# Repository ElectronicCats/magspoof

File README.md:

# MagSpoof By Electronic Cats
  
<a href="https://github.com/ElectronicCats/magspoof/wiki">

<p align=center>

</p>

<p align=center>
Also available at distributors:
</p>
<p align=center>

</p>

# What is MagSpoof?

**MagSpoof by Electronic Cats** is a device that can spoof/emulate any magnetic stripe or credit card. It can work "wirelessly", even on **standard magstripe/credit card readers**, by generating a strong electromagnetic field that emulates a traditional magnetic stripe card.

* Allows you to store all of your credit cards and magstripes in one device
* Works on traditional magstripe readers **wirelessly** (no NFC/RFID required)
* Can **disable** Chip-and-PIN (code not included)
* Correctly **predicts** Amex credit card numbers + expirations from previous card number (code not included)
* Supports all three magnetic stripe tracks, and even supports Track 1+2 simultaneously
* Easy to build using Arduino or other common parts

MagSpoof can be used as a traditional credit card and simply store all of your credit cards (and with modification, can technically disable chip requirements) in various impressive and exciting form factors, or can be used for security research in any area that would traditionally require a magstripe, such as readers for credit cards, drivers licenses, hotel room keys, automated parking lot tickets, etc.

**Note**: The Chip-and-PIN and Amex information is **not** implemented and using MagSpoof requires you to have/own the magstripes that you wish to emulate. Simply having a credit card number and expiration is not enough to perform transactions. MagSpoof **does** allow you to perform research in other areas of magstripes, microcontrollers, and electromagnetism, as well as learn about and create your own devices similar to other existing, commercial technologies such as <a href="http://www.samsung.com/us/support/answer/ANS00043865/997410383/">Samsung MST</a> and <a href="https://onlycoin.com/">Coin</a>.</p>

### ⚠️ Disclaimer ⚠️
MagSpoof is a wireless penetration testing tool intended solely for use in authorized security audits, where such usage is permitted by applicable laws and regulations. Before utilizing this tool, it is crucial to ensure compliance with all relevant legal requirements and obtain appropriate permissions from the relevant authorities.

It is essential to notice that the board does not provide any means or authorization to utilize credit cards or engage in any financial transactions that are not legally authorized. Electronic Cats holds no responsibility for any unauthorized use of the tool or any resulting damages.

-----

# Based in work of Samy Kamkar

**Point of Contact:** [@SamyKamkar](https://twitter.com/samykamkar)

You can see more of my projects at <http://samy.pl> or contact me at <code@samy.pl>.

------

## How to contribute 
 Contributions are welcome! 

Please read the document  [**Contribution Manual**](https://github.com/ElectronicCats/electroniccats-cla/blob/main/electroniccats-contribution-manual.md)  which will show you how to contribute your changes to the project.

✨ Thanks to all our [contributors](https://github.com/ElectronicCats/magspoof/graphs/contributors)! ✨

See  [**_Electronic Cats CLA_**](https://github.com/ElectronicCats/electroniccats-cla/blob/main/electroniccats-cla.md) for more information.

See the [**community code of conduct**](https://github.com/ElectronicCats/electroniccats-cla/blob/main/electroniccats-community-code-of-conduct.md)   for a vision of the community we want to build and what we expect from it.

### Maintainer

Electronic Cats invests time and resources in providing this open-source design design, please support Electronic Cats and open-source hardware by purchasing products from Electronic Cats!

# License

Electronic Cats invests time and resources in providing this open-source design. Please support Electronic Cats and open-source hardware by purchasing products from Electronic Cats!

Designed by Electronic Cats.

Firmware released under an GNU AGPL v3.0 license. See the LICENSE file for more information.

Hardware released under an CERN Open Hardware Licence v1.2. See the LICENSE_HARDWARE file for more information.

Electronic Cats is a registered trademark, please do not use if you sell these PCBs.

30 Octuber 2019

------

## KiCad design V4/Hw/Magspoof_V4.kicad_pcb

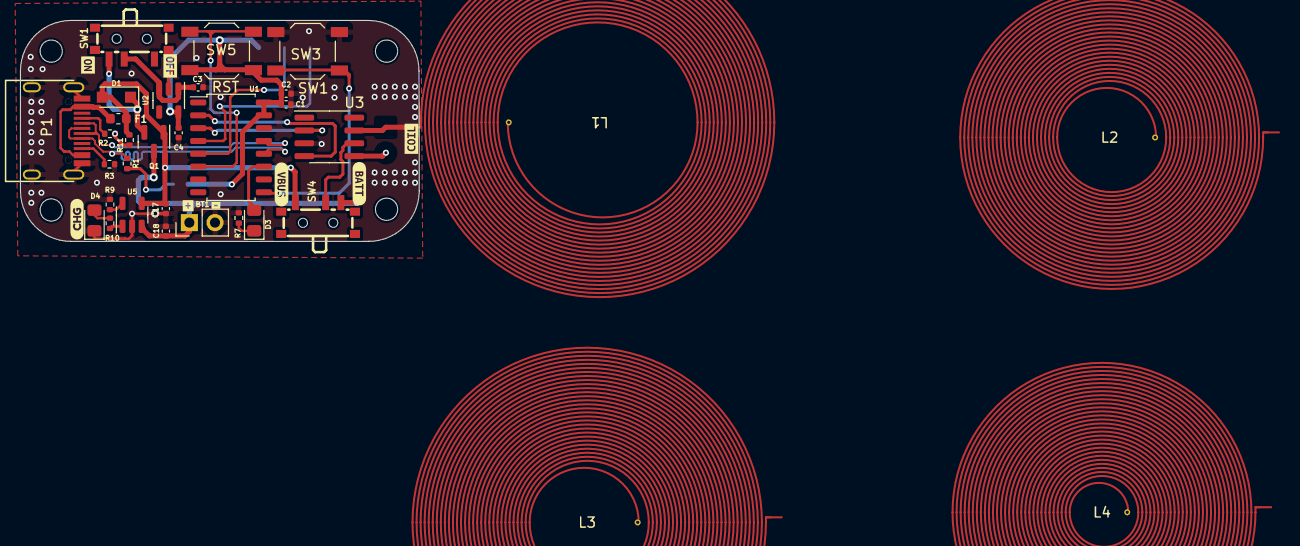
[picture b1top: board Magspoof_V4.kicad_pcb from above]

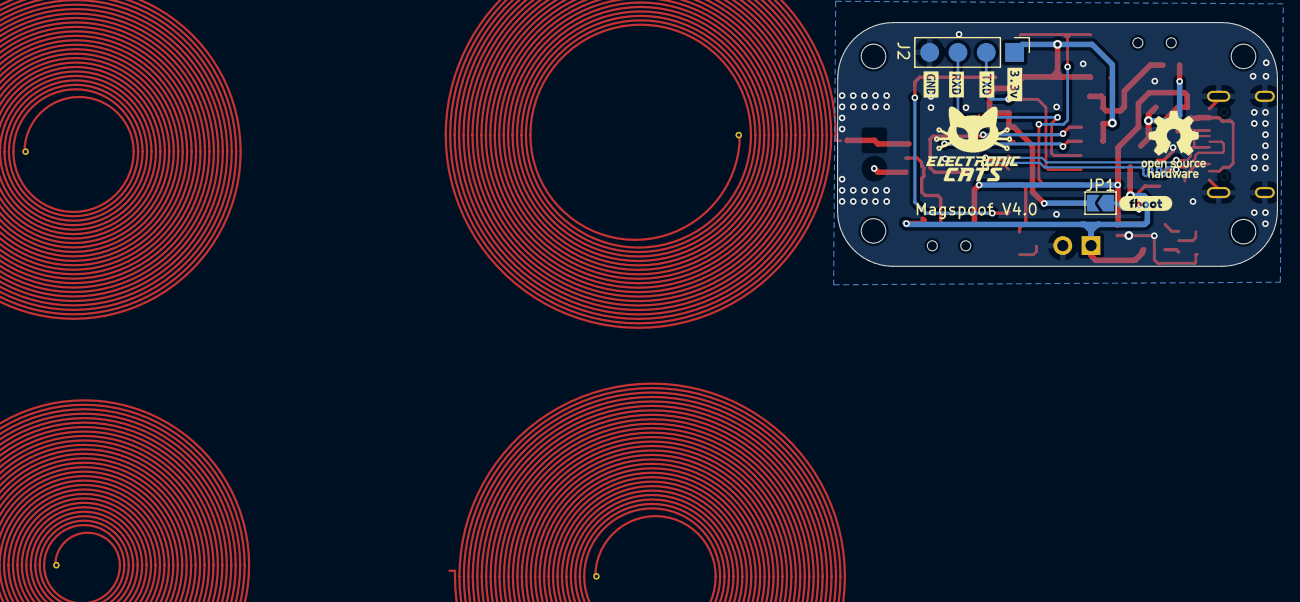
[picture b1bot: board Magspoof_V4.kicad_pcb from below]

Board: 2 copper layers, 39.5 x 21.9 mm, 51 parts (7 on the bottom side), 25 nets.

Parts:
BT1: Battery_Cell; PinHeader_1x02_P2.54mm_Vertical
C1, C2: 0.1uF; C_0402_1005Metric
C3, C4, C17, C18: 10uF; C_0402_1005Metric
D1: MBR120; D_SOD-123F
D3: Status; LED_0805_2012Metric_Pad1.15x1.40mm_HandSolder
D4: CHG; LED_0805_2012Metric_Pad1.15x1.40mm_HandSolder
F1: 0.5A; Fuse_0603_1608Metric
H1, H2, H3, H4: MountingHole; MountingHole_2.2mm_M2
J2: SWD; PinHeader_1x04_P2.54mm_Vertical
JP1: boot; SolderJumper-2_P1.3mm_Open_TrianglePad1.0x1.5mm
L1: 20t_35mm; Coil_20t_35mm_0.2_0.2_0.6_0.3
L2: 25t_30mm; Coil_25t_30mm_0.2_0.2_0.6_0.3
L3: 30t_35mm; Coil_30t_35mm_0.2_0.2_0.6_0.3
L4: 30t_30mm; Coil_30t_30mm_0.2_0.2_0.6_0.3
P1: USB_C_Plug_USB2.0; C393939
Q1: DMG3415U-7; SOT-23
R1: 20K; R_0402_1005Metric
R2, R3, R9: 5.1k; R_0402_1005Metric
R7: 180R; R_0402_1005Metric
R10: 470; R_0402_1005Metric
R11: 100K; R_0402_1005Metric
SW1: ON; SW-SMD_SSSS811101
SW3: S1; SW_SPST_TL3342
SW4: SOURCE MAG; SW-SMD_SSSS811101
SW5: RESET; SW_SPST_TL3342
U1: CH552G; SOP-16_4.55x10.3mm_P1.27mm
U2: AP2112K-3.3; SOT-23-5
U3: TC4424; SOIC-8_3.9x4.9mm_P1.27mm
U5: MCP73831; SOT-23-5
kibuzzard-6435F1C7: G***; kibuzzard-6435F1C7
kibuzzard-6435F3C4: G***; kibuzzard-6435F3C4
kibuzzard-6435F22E: G***; kibuzzard-6435F22E
kibuzzard-6436E8D1: G***; kibuzzard-6436E8D1
kibuzzard-6436E8D8: G***; kibuzzard-6436E8D8
kibuzzard-6436EA37: G***; kibuzzard-6436EA37
kibuzzard-6436EA46: G***; kibuzzard-6436EA46
kibuzzard-6436EF9F: G***; kibuzzard-6436EF9F
kibuzzard-6436EF98: G***; kibuzzard-6436EF98
kibuzzard-64629FC5: G***; kibuzzard-64629FC5
kibuzzard-64629FDC: G***; kibuzzard-64629FDC
kibuzzard-64665C6A: G***; kibuzzard-64665C6A
kibuzzard-64665C9F: G***; kibuzzard-64665C9F

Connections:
+3V3: C1.1, C2.1, C4.1, J2.1, JP1.2 (B), SW5.2, U1.15 (VCC), U1.16 (V33), U2.5 (VOUT)
+BATT: BT1.1 (+), C18.1, Q1.3 (D), SW4.3 (C), U5.3 (VBAT)
/D+: P1.A6 (D+), R1.2, U1.12 (P3.6)
/D-: P1.A7 (D-), U1.13 (P3.7)
/IN_A: U1.2 (P1.4), U3.4 (IN_B)
/IN_B: U1.3 (P1.5), U3.2 (IN_A)
/LED: D3.2 (A), U1.11 (P3.4)
/Out_A: L1.1, L2.1, L3.1, L4.1, U3.7 (OUT_A)
/RST: SW5.1, U1.6 (RST)
/RXD: J2.3, U1.4 (P1.6)
/SW1: SW3.2, U1.9 (P1.1)
/TXD: J2.2, U1.5 (P1.7)
GND: BT1.2 (-), C1.2, C2.2, C3.2, C4.2, C17.2, C18.2, D4.1 (K), J2.4, P1.A1 (GND), P1.S1 (SHIELD), R2.1, R3.1, R7.2, R9.2, R11.2, SW3.1, U1.14 (GND), U2.2 (GND), U3.3 (GND), U5.2 (VSS)
unnamed: D1.1 (K), Q1.2 (S), SW1.3 (A)
unnamed: D3.1 (K), R7.1
unnamed: D4.2 (A), R10.2
unnamed: F1.1, P1.A4 (VBUS)
unnamed: JP1.1 (A), R1.1
unnamed: P1.A5 (CC), R2.2
unnamed: P1.B5 (VCONN), R3.2
unnamed: C3.1, SW1.2 (B), U2.1 (VIN), U2.3 (EN)
unnamed: SW4.2 (B), U3.6 (VDD)
unnamed: R9.1, U5.5 (PROG)
unnamed: R10.1, U5.1 (STAT)
VBUS: C17.1, D1.2 (A), F1.2, Q1.1 (G), R11.1, SW4.1 (A), U5.4 (VDD)

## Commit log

2023-12-19 Update README.md
    Pictures removed
2023-12-20 Update README.md
    Changes:
    1.- Adding pictures of the device to the presentation and wiki section
    2.- Adding pictures with links to the store and wiki
2023-12-20 Update README.md
    Changes:
    1.- Adding pictures of the device to the general description and wiki section.
    2.- Adding links to the store and the wiki
    3.- Adding picture for the license
2023-12-21 Update README.md
    Changes in the button to the store
2023-12-26 Update README.md
    Rearrange of pictures with links to the store and wiki
2024-01-09 Add_Step_File
2024-03-05 feat: flat spiral coil proposals for PCB antenna
2024-03-06 chore: update .gitignore
2024-03-06 feat(hw): add library
2024-03-11 feat(hw): add 2 additional coils and the specs of the coils
2024-03-20 feat(hw): add Test coils panel
2024-03-20 fix(hw): route correction
2024-03-20 feat(hw): panelizing
2024-03-21 fix(hw): change edge cuts
2024-03-21 fix(hw): update edge cuts
2024-03-22 fix(hw): panelization changes
2024-04-04 feat(hw): Magspoof V5 pcb and layaout added
2024-04-05 Create LICENSE_HARDWARE
2024-04-08 feat(hw): components got reorganized
2024-04-08 feat(hw): TX and RX pins updated
2024-04-08 feat(hw): path width changed
2024-04-09 feat (docs): Update README.md
    How to contribute added
2024-04-09 fix(hw): Some paths got corrections
2024-04-09 fix(hw): pins Serial boot
2024-04-09 feat(hw): add logos
2024-04-10 feat(hw): added TX and RX Boot pins
2024-04-10 feat(hw): logos
2024-04-11 feat(hw): components organization updated
2024-04-11 feat(hw): BOM generated
2024-04-11 fix(hw): orientation logo
2024-04-11 feat(hw): move label batt
2024-04-11 feat(hw): BOM got updated
2024-04-11 feat(hw): USB manufacture part updated
2024-04-11 fix(hw): layer correction of dimension comments
2024-04-24 feat(docs): add distributor button
2024-04-24 feat(docs): add text and distributor button
2024-05-02 feat: testing firmware added
2024-05-09 chore: added comments
2024-05-13 feat: added serialComplete var
2024-05-15 feat: add path for firmware
2024-05-16 feat: added help menu
2024-06-26 fix(hw): DNP update of the list components
2024-07-01 fix(hw): change path test coils
2024-07-01 fix: remove code comments
2024-07-02 fix: NL and CR ok
2024-07-02 feat: add showEEPROM()
2024-07-15 feat: load contents from EEPROM
2024-07-16 fix: typo name
2024-07-23 feat (docs): Update README.md
    Updated to Magspoof V5.
2024-07-25 feat (docs): Update README.md
2024-07-30 feat: update example allinone v4
2024-10-28 Fix: typo
2025-04-02 feat(hw); add STL case files
